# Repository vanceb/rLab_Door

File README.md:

# rLab_Door
A microcontroller project to allow members access to rLab

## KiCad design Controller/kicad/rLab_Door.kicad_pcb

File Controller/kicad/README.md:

# Production

## Kikit

Instructions for [kikit JLCPCB](https://github.com/yaqwsx/KiKit/blob/master/doc/fabrication/jlcpcb.md)

~~~sh
kikit fab jlcpcb --assembly --schematic rLab_Door.kicad_sch rLab_Door.kicad_pcb kikit_fab
~~~

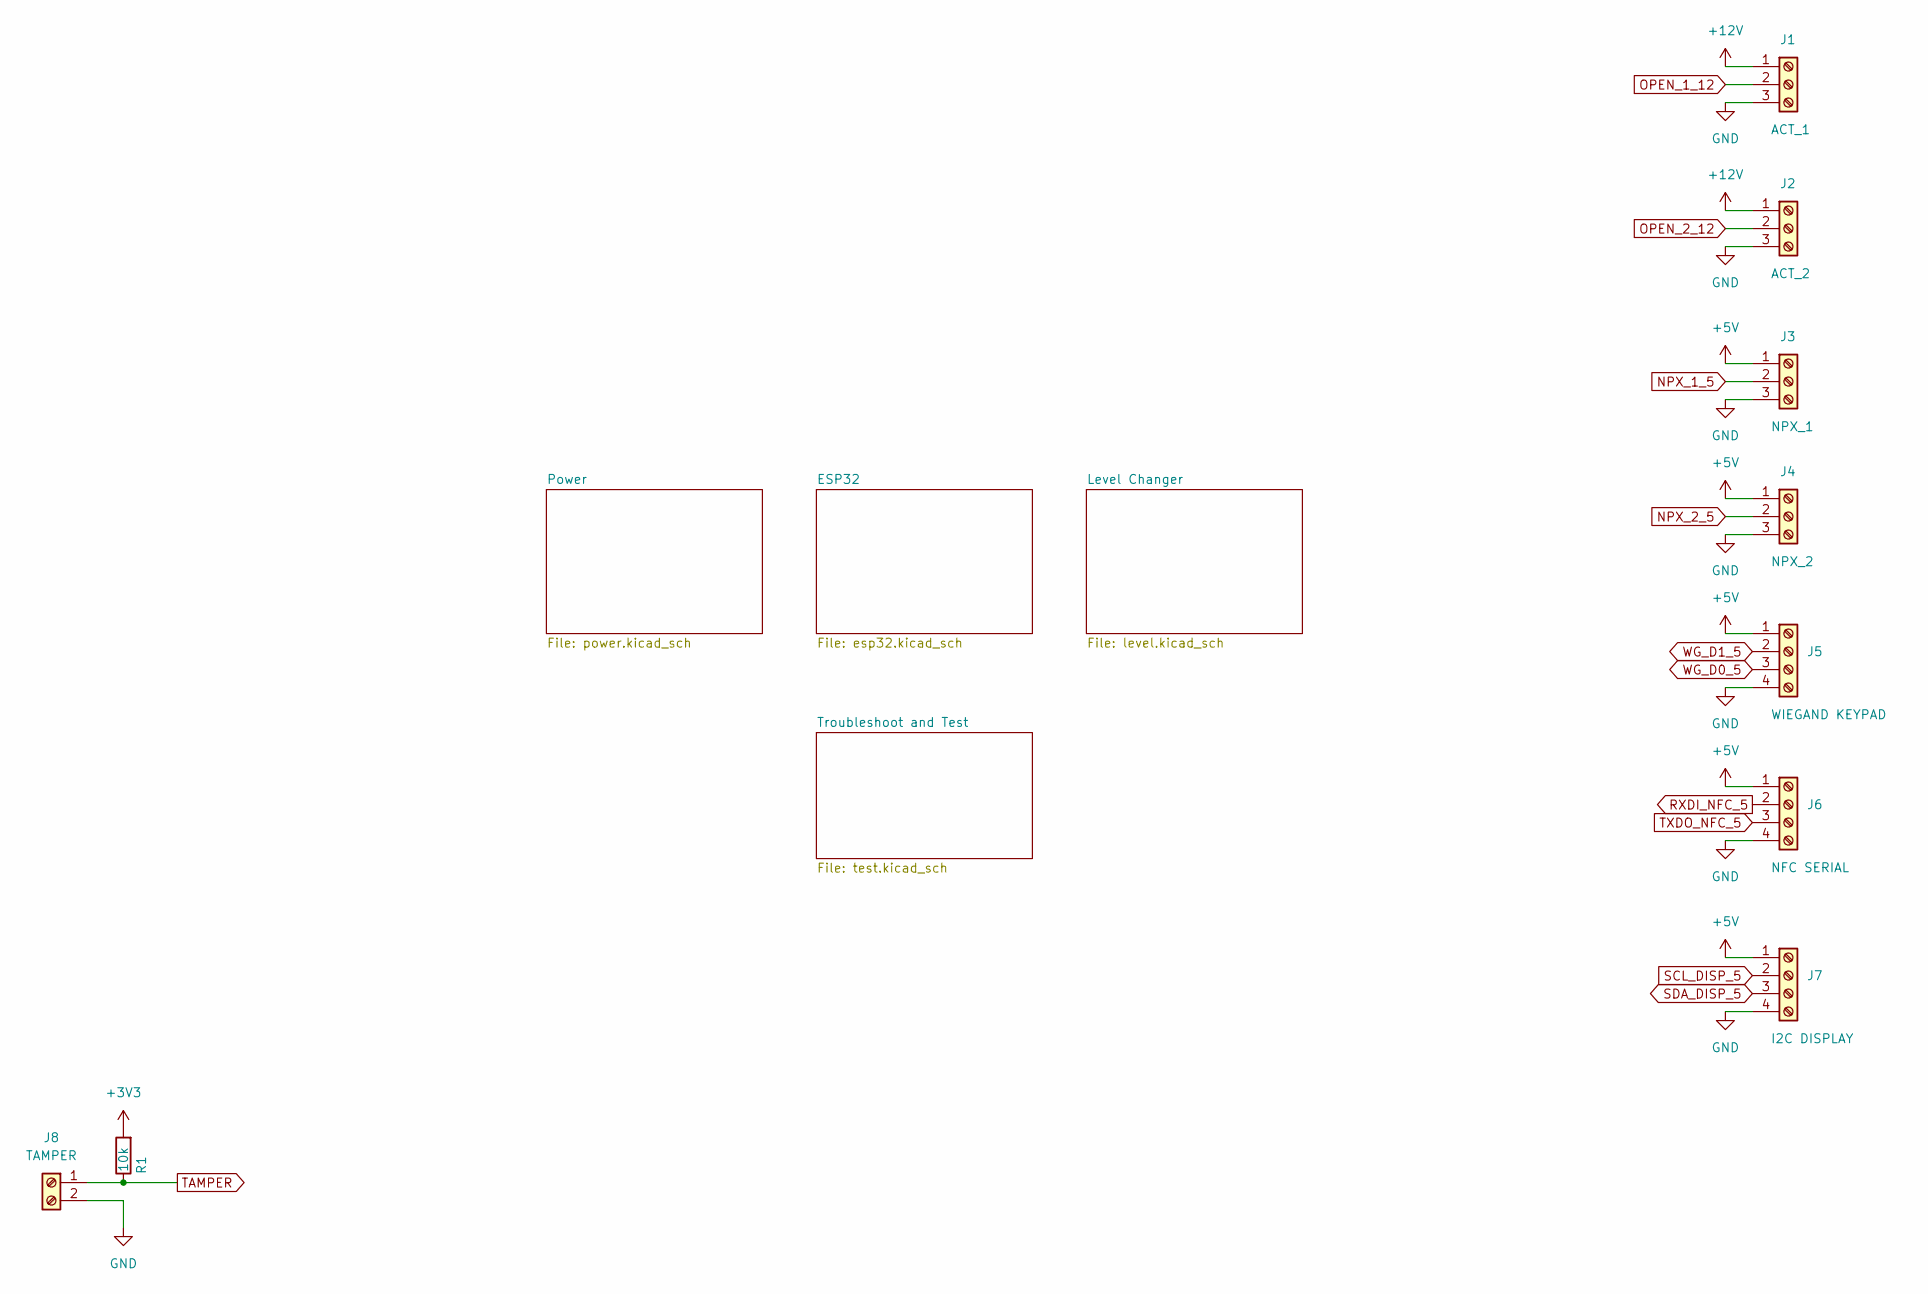
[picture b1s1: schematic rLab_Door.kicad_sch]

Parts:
J1: ACT_1; PinHeader_1x03_P2.54mm_Horizontal
J2: ACT_2; PinHeader_1x03_P2.54mm_Horizontal
J3: NPX_1; PinHeader_1x03_P2.54mm_Horizontal
J4: NPX_2; PinHeader_1x03_P2.54mm_Horizontal
J5: WIEGAND KEYPAD; PinHeader_1x04_P2.54mm_Horizontal
J6: NFC SERIAL; PinHeader_1x04_P2.54mm_Horizontal
J7: I2C DISPLAY; PinHeader_1x04_P2.54mm_Horizontal
J8: TAMPER; PinHeader_1x02_P2.54mm_Horizontal
R1: 10k; R_0603_1608Metric; LCSC C25804

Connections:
+3V3: R1.2; also elsewhere on the board
+5V: J3.1, J4.1, J5.1, J6.1, J7.1; also elsewhere on the board
+12V: J1.1, J2.1; also elsewhere on the board
GND: J1.3, J2.3, J3.3, J4.3, J5.4, J6.4, J7.4, J8.2; also elsewhere on the board
NPX_1_5: J3.2; also elsewhere on the board
NPX_2_5: J4.2; also elsewhere on the board
OPEN_1_12: J1.2; also elsewhere on the board
OPEN_2_12: J2.2; also elsewhere on the board
RXDI_NFC_5: J6.2; also elsewhere on the board
SCL_DISP_5: J7.2; also elsewhere on the board
SDA_DISP_5: J7.3; also elsewhere on the board
TAMPER: J8.1, R1.1; also elsewhere on the board
TXDO_NFC_5: J6.3; also elsewhere on the board
WG_D0_5: J5.3; also elsewhere on the board
WG_D1_5: J5.2; also elsewhere on the board

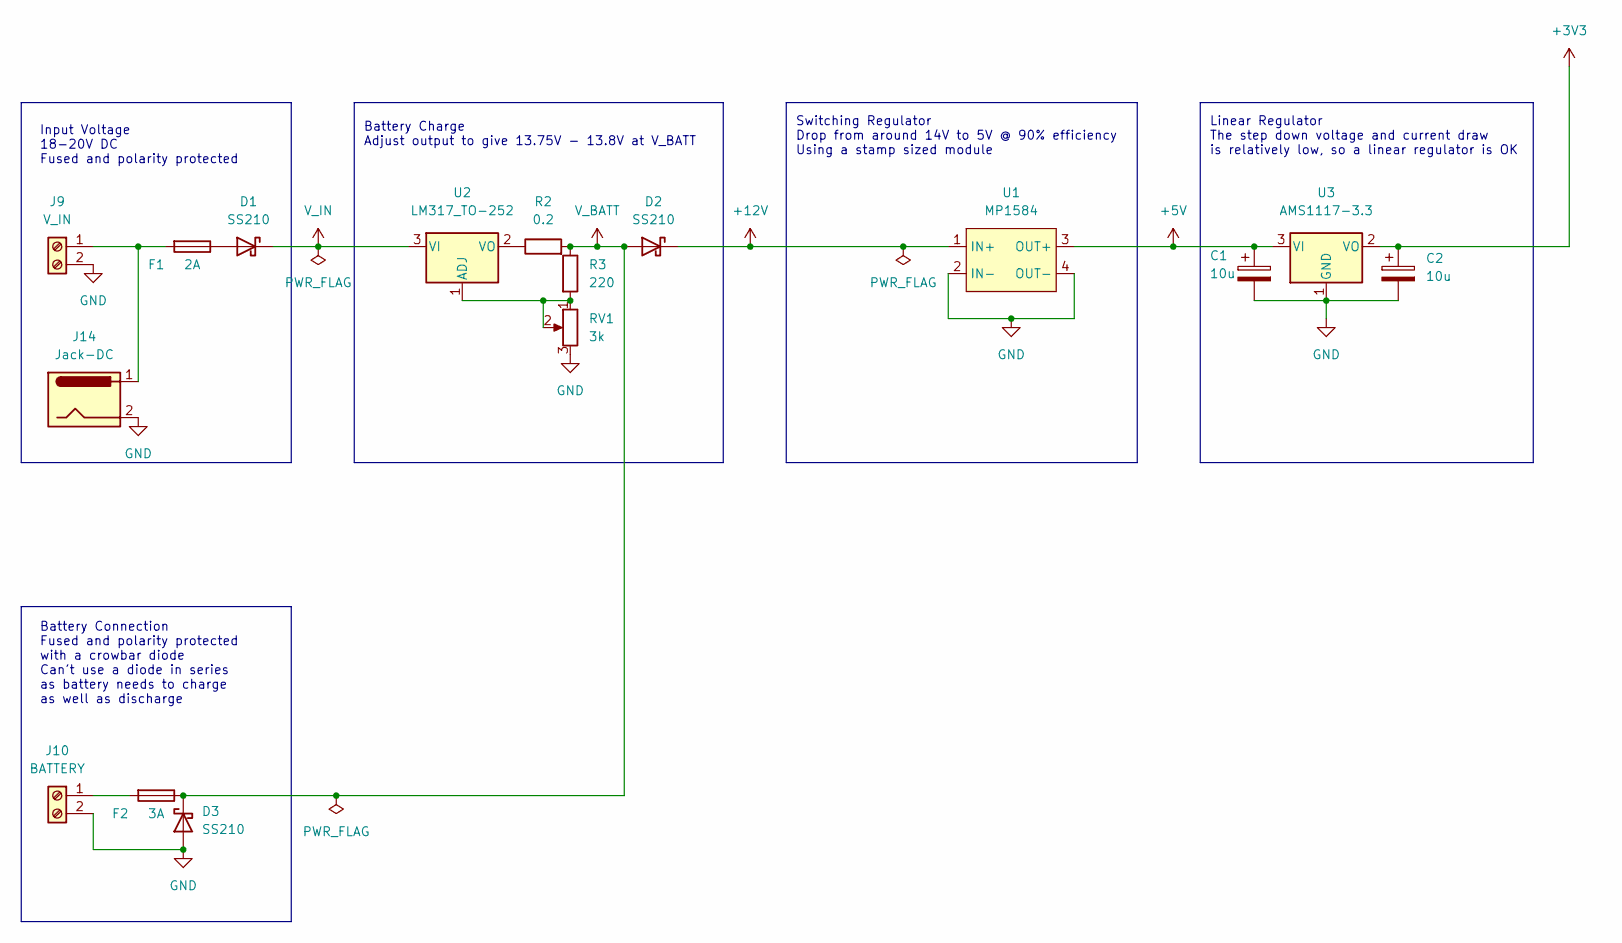
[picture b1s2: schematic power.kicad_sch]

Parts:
C1, C2: 10u; CP_EIA-3216-18_Kemet-A; LCSC C7171
D1, D2, D3: SS210; D_SMA; LCSC C14996
F1: 2A; Fuseholder_Cylinder-5x20mm_Schurter_0031_8201_Horizontal_Op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
F2: 3A; Fuseholder_Cylinder-5x20mm_Schurter_0031_8201_Horizontal_Op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
J9: V_IN; PinHeader_1x02_P2.54mm_Horizontal
J10: BATTERY; PinHeader_1x02_P2.54mm_Horizontal
J14: Jack-DC; BarrelJack_Horizontal
R2: 0.2; R_2512_6332Metric_Pad1.40x3.35mm_HandSolder; LCSC C841782
R3: 220; R_0603_1608Metric; LCSC C22962
RV1: 3k; Potentiometer_Bourns_3296W_Vertical
U1: MP1584
U2: LM317_TO-252; TO-252-2; LCSC C75510
U3: AMS1117-3.3; SOT-223-3_TabPin2; LCSC C6186

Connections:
+3V3: C2.1, U3.2 (VO); also elsewhere on the board
+5V: C1.1, U1.3 (OUT+), U3.3 (VI); also elsewhere on the board
+12V: D2.1 (K), U1.1 (IN+); also elsewhere on the board
GND: C1.2, C2.2, D3.2 (A), J9.2, J10.2, J14.2, RV1.3, U1.2 (IN-), U1.4 (OUT-), U3.1 (GND); also elsewhere on the board
unnamed: D1.2 (A), F1.1
unnamed: F1.2, J9.1, J14.1
unnamed: F2.2, J10.1
unnamed: R2.1, U2.2 (VO)
unnamed: R3.2, RV1.1, RV1.2, U2.1 (ADJ)
V_BATT: D2.2 (A), D3.1 (K), F2.1, R2.2, R3.1; also elsewhere on the board
V_IN: D1.1 (K), U2.3 (VI); also elsewhere on the board

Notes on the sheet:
Battery Charge Adjust output to give 13.75V - 13.8V at V_BATT
Linear Regulator The step down voltage and current draw is relatively low, so a linear regulator is OK
Battery Connection Fused and polarity protected with a crowbar diode Can't use a diode in series as battery needs to charge as well as discharge
Switching Regulator Drop from around 14V to 5V @ 90% efficiency Using a stamp sized module
Input Voltage 18-20V DC Fused and polarity protected

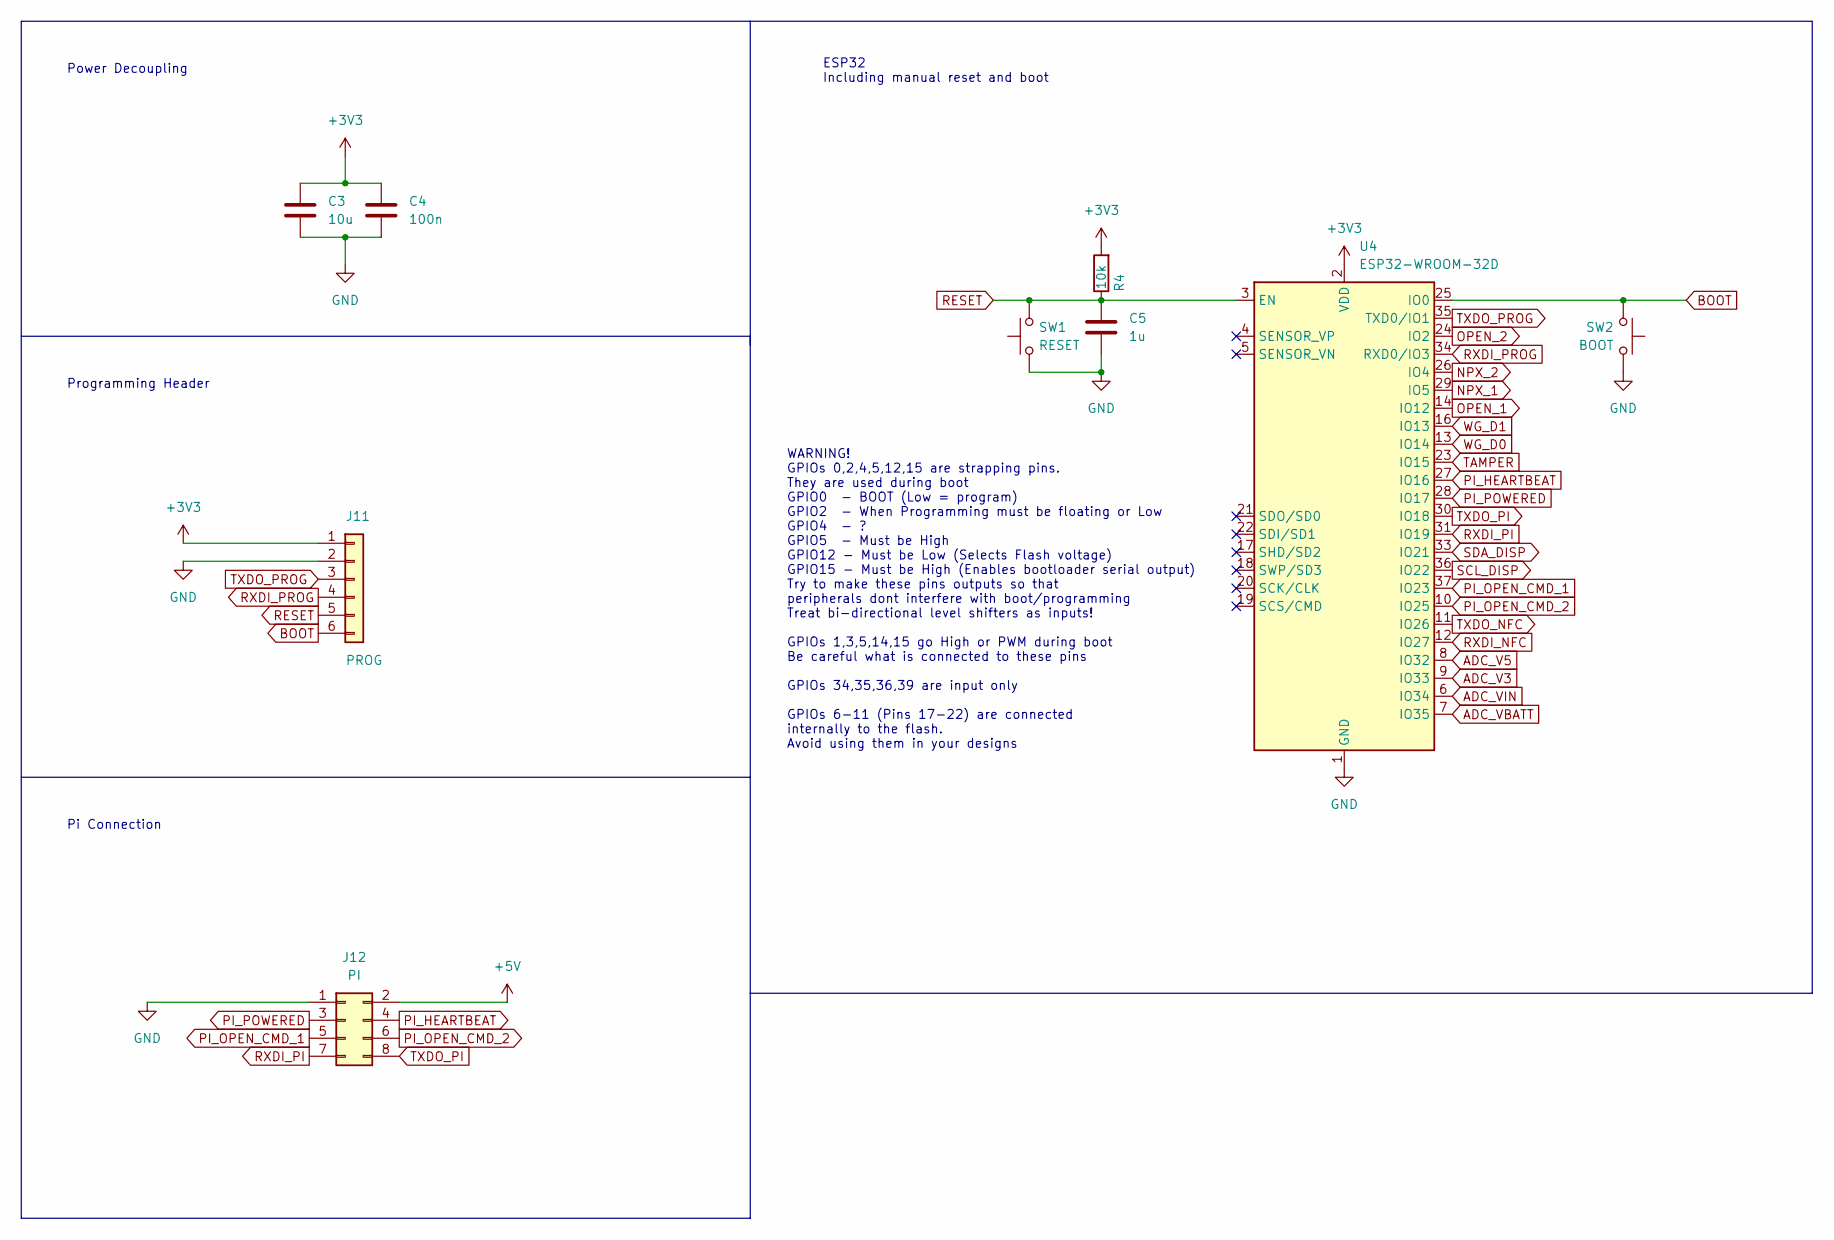
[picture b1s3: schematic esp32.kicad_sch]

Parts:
C3: 10u; C_1206_3216Metric; LCSC C13585
C4: 100n; C_0603_1608Metric; LCSC C14663
C5: 1u; C_0603_1608Metric; LCSC C15849
J11: PROG; PinHeader_1x06_P2.54mm_Vertical
J12: PI; IDC-Header_2x04_P2.54mm_Vertical
R4: 10k; R_0603_1608Metric; LCSC C25804
SW1: RESET; SW_Push_1P1T_NO_CK_KSC7xxJ; LCSC C318884
SW2: BOOT; SW_Push_1P1T_NO_CK_KSC7xxJ; LCSC C318884
U4: ESP32-WROOM-32D; ESP32-WROOM-32; LCSC C473012

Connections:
+3V3: C3.1, C4.1, J11.1, R4.2, U4.2 (VDD); also elsewhere on the board
+5V: J12.2; also elsewhere on the board
ADC_V3: U4.9 (IO33); also elsewhere on the board
ADC_V5: U4.8 (IO32); also elsewhere on the board
ADC_VBATT: U4.7 (IO35); also elsewhere on the board
ADC_VIN: U4.6 (IO34); also elsewhere on the board
BOOT: J11.6, SW2.2, U4.25 (IO0)
GND: C3.2, C4.2, C5.2, J11.2, J12.1, SW1.1, SW2.1, U4.1 (GND), U4.15 (GND), U4.38 (GND), U4.39 (GND); also elsewhere on the board
NPX_1: U4.29 (IO5); also elsewhere on the board
NPX_2: U4.26 (IO4); also elsewhere on the board
OPEN_1: U4.14 (IO12); also elsewhere on the board
OPEN_2: U4.24 (IO2); also elsewhere on the board
PI_HEARTBEAT: J12.4, U4.27 (IO16)
PI_OPEN_CMD_1: J12.5, U4.37 (IO23)
PI_OPEN_CMD_2: J12.6, U4.10 (IO25)
PI_POWERED: J12.3, U4.28 (IO17)
RESET: C5.1, J11.5, R4.1, SW1.2, U4.3 (EN)
RXDI_NFC: U4.12 (IO27); also elsewhere on the board
RXDI_PI: J12.7, U4.31 (IO19)
RXDI_PROG: J11.4, U4.34 (RXD0/IO3)
SCL_DISP: U4.36 (IO22); also elsewhere on the board
SDA_DISP: U4.33 (IO21); also elsewhere on the board
TAMPER: U4.23 (IO15); also elsewhere on the board
TXDO_NFC: U4.11 (IO26); also elsewhere on the board
TXDO_PI: J12.8, U4.30 (IO18)
TXDO_PROG: J11.3, U4.35 (TXD0/IO1)
WG_D0: U4.13 (IO14); also elsewhere on the board
WG_D1: U4.16 (IO13); also elsewhere on the board

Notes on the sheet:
Pi Connection
ESP32 Including manual reset and boot
Programming Header
WARNING! GPIOs 0,2,4,5,12,15 are strapping pins. They are used during boot GPIO0 - BOOT (Low = program) GPIO2 - When Programming must be floating or Low GPIO4 - ? GPIO5 - Must be High GPIO12 - Must be Low (Selects Flash voltage) GPIO15 - Must be High (Enables bootloader serial output) Try to make t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
Power Decoupling

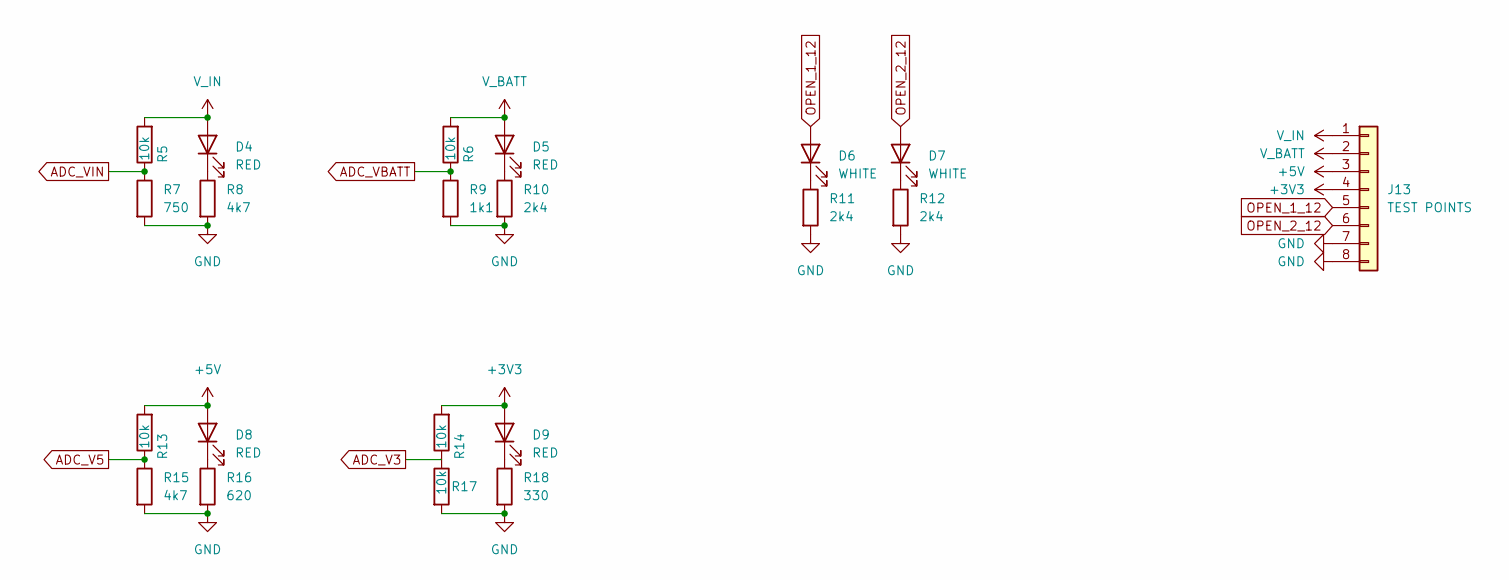
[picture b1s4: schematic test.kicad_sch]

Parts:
D4, D5, D8, D9: RED; LED_0603_1608Metric; LCSC C2286
D6, D7: WHITE; LED_0603_1608Metric; LCSC C2290
J13: TEST POINTS; PinHeader_1x08_P2.54mm_Vertical
R5, R6, R13, R14, R17: 10k; R_0603_1608Metric; LCSC C25804
R7: 750; R_0603_1608Metric; LCSC C23241
R8, R15: 4k7; R_0603_1608Metric; LCSC C23162
R9: 1k1; R_0603_1608Metric; LCSC C22764
R10, R11, R12: 2k4; R_0603_1608Metric; LCSC C22940
R16: 620; R_0603_1608Metric; LCSC C23220
R18: 330; R_0603_1608Metric; LCSC C23138

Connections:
+3V3: D9.2 (A), J13.4, R14.2; also elsewhere on the board
+5V: D8.2 (A), J13.3, R13.2; also elsewhere on the board
ADC_V3: R14.1, R17.1; also elsewhere on the board
ADC_V5: R13.1, R15.1; also elsewhere on the board
ADC_VBATT: R6.1, R9.1; also elsewhere on the board
ADC_VIN: R5.1, R7.1; also elsewhere on the board
GND: J13.7, J13.8, R7.2, R8.2, R9.2, R10.2, R11.2, R12.2, R15.2, R16.2, R17.2, R18.2; also elsewhere on the board
unnamed: D4.1 (K), R8.1
unnamed: D5.1 (K), R10.1
unnamed: D6.1 (K), R11.1
unnamed: D7.1 (K), R12.1
unnamed: D8.1 (K), R16.1
unnamed: D9.1 (K), R18.1
OPEN_1_12: D6.2 (A), J13.5; also elsewhere on the board
OPEN_2_12: D7.2 (A), J13.6; also elsewhere on the board
V_BATT: D5.2 (A), J13.2, R6.2; also elsewhere on the board
V_IN: D4.2 (A), J13.1, R5.2; also elsewhere on the board

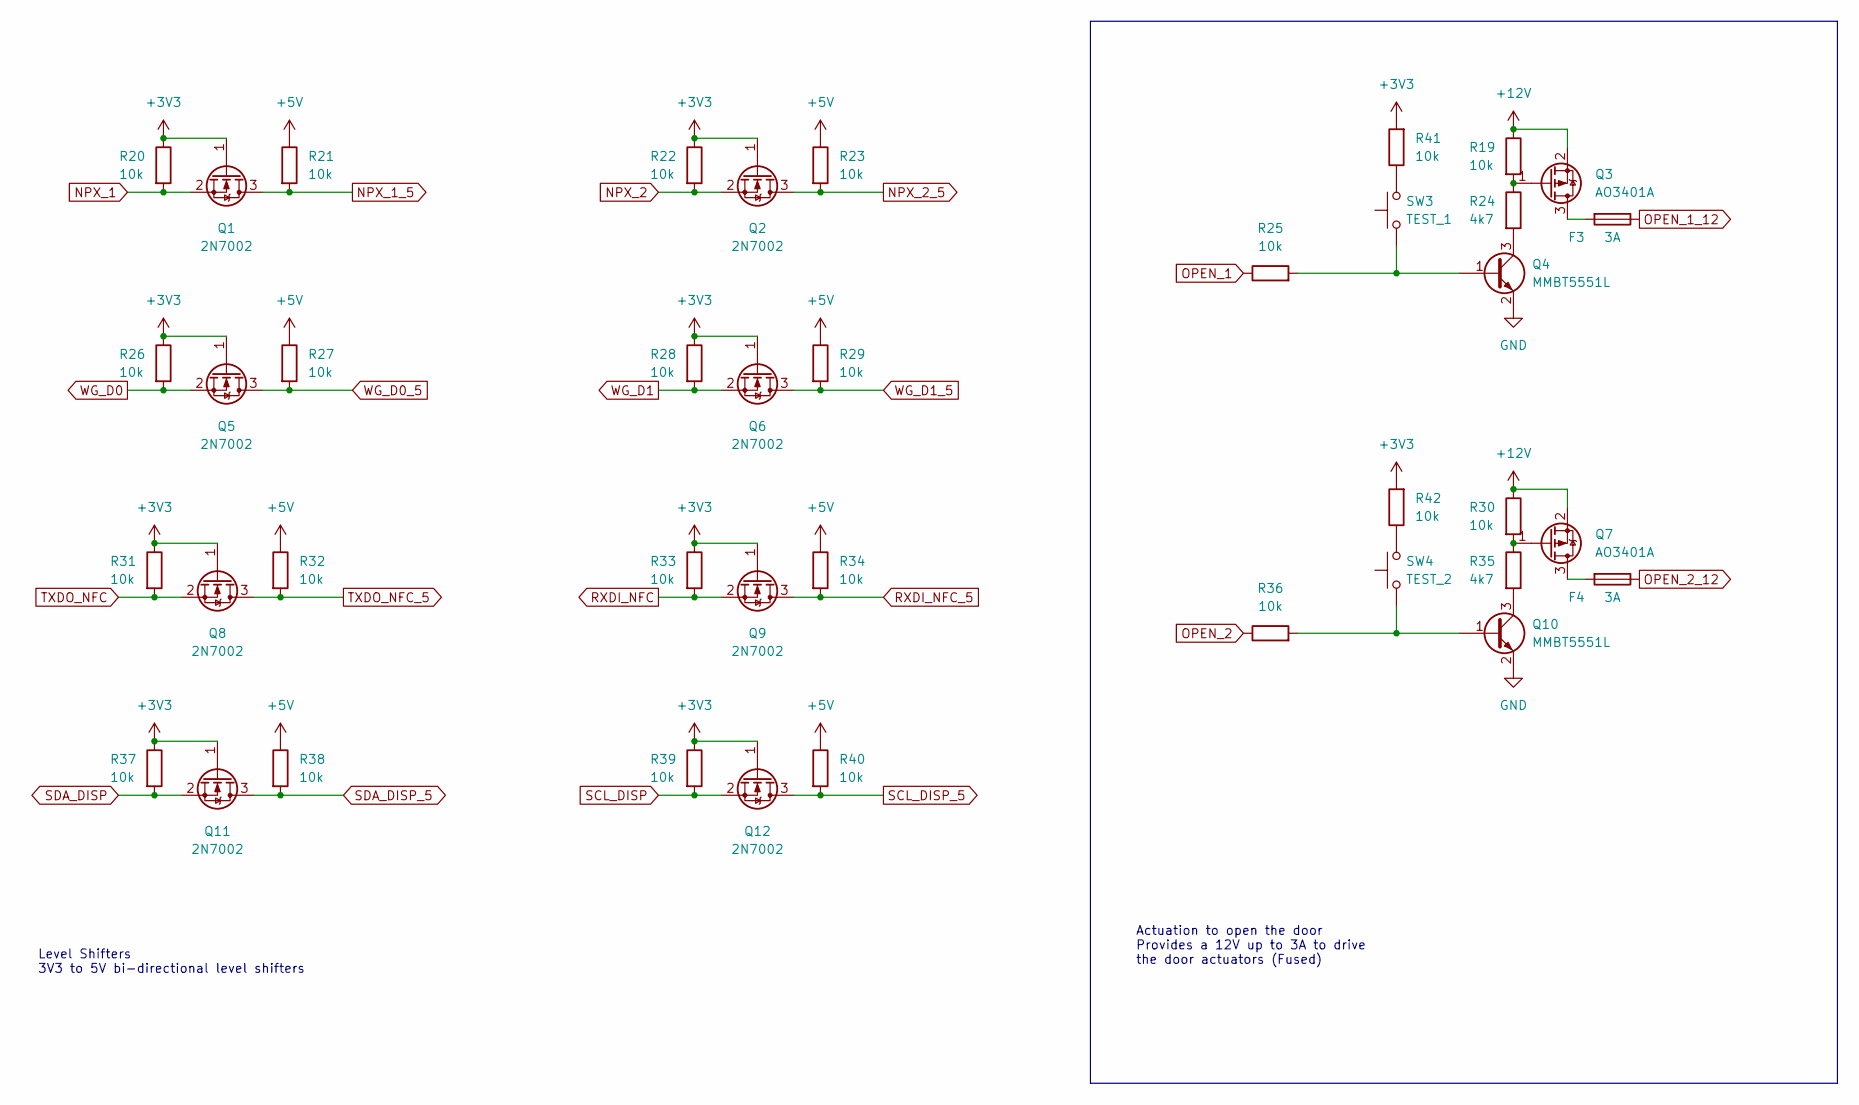
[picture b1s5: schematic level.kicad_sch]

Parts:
F3, F4: 3A; Fuseholder_Cylinder-5x20mm_Schurter_0031_8201_Horizontal_Op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
Q1, Q2, Q5, Q6, Q8, Q9, Q11, Q12: 2N7002; SOT-23; LCSC C8545
Q3, Q7: AO3401A; SOT-23; LCSC C15127
Q4, Q10: MMBT5551L; SOT-23; LCSC C2145
R19, R20, R21, R22, R23, R25, R26, R27, R28, R29, R30, R31, R32, R33, R34, R36, R37, R38, R39, R40, R41, R42: 10k; R_0603_1608Metric; LCSC C25804
R24, R35: 4k7; R_0603_1608Metric; LCSC C23162
SW3: TEST_1; SW_Push_1P1T_NO_CK_KSC7xxJ; LCSC C318884
SW4: TEST_2; SW_Push_1P1T_NO_CK_KSC7xxJ; LCSC C318884

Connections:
+3V3: Q1.1 (G), Q2.1 (G), Q5.1 (G), Q6.1 (G), Q8.1 (G), Q9.1 (G), Q11.1 (G), Q12.1 (G), R20.1, R22.1, R26.1, R28.1, R31.1, R33.1, R37.1, R39.1, R41.2, R42.2; also elsewhere on the board
+5V: R21.1, R23.1, R27.1, R29.1, R32.1, R34.1, R38.1, R40.1; also elsewhere on the board
+12V: Q3.2 (S), Q7.2 (S), R19.1, R30.1; also elsewhere on the board
GND: Q4.2 (E), Q10.2 (E); also elsewhere on the board
NPX_1: Q1.2 (S), R20.2; also elsewhere on the board
NPX_1_5: Q1.3 (D), R21.2; also elsewhere on the board
NPX_2: Q2.2 (S), R22.2; also elsewhere on the board
NPX_2_5: Q2.3 (D), R23.2; also elsewhere on the board
unnamed: F3.2, Q3.3 (D)
unnamed: F4.2, Q7.3 (D)
unnamed: Q3.1 (G), R19.2, R24.1
unnamed: Q4.1 (B), R25.2, SW3.1
unnamed: Q4.3 (C), R24.2
unnamed: Q7.1 (G), R30.2, R35.1
unnamed: Q10.1 (B), R36.2, SW4.1
unnamed: Q10.3 (C), R35.2
unnamed: R41.1, SW3.2
unnamed: R42.1, SW4.2
OPEN_1: R25.1; also elsewhere on the board
OPEN_1_12: F3.1; also elsewhere on the board
OPEN_2: R36.1; also elsewhere on the board
OPEN_2_12: F4.1; also elsewhere on the board
RXDI_NFC: Q9.2 (S), R33.2; also elsewhere on the board
RXDI_NFC_5: Q9.3 (D), R34.2; also elsewhere on the board
SCL_DISP: Q12.2 (S), R39.2; also elsewhere on the board
SCL_DISP_5: Q12.3 (D), R40.2; also elsewhere on the board
SDA_DISP: Q11.2 (S), R37.2; also elsewhere on the board
SDA_DISP_5: Q11.3 (D), R38.2; also elsewhere on the board
TXDO_NFC: Q8.2 (S), R31.2; also elsewhere on the board
TXDO_NFC_5: Q8.3 (D), R32.2; also elsewhere on the board
WG_D0: Q5.2 (S), R26.2; also elsewhere on the board
WG_D0_5: Q5.3 (D), R27.2; also elsewhere on the board
WG_D1: Q6.2 (S), R28.2; also elsewhere on the board
WG_D1_5: Q6.3 (D), R29.2; also elsewhere on the board

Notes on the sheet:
Level Shifters 3V3 to 5V bi-directional level shifters
Actuation to open the door Provides a 12V up to 3A to drive the door actuators (Fused)

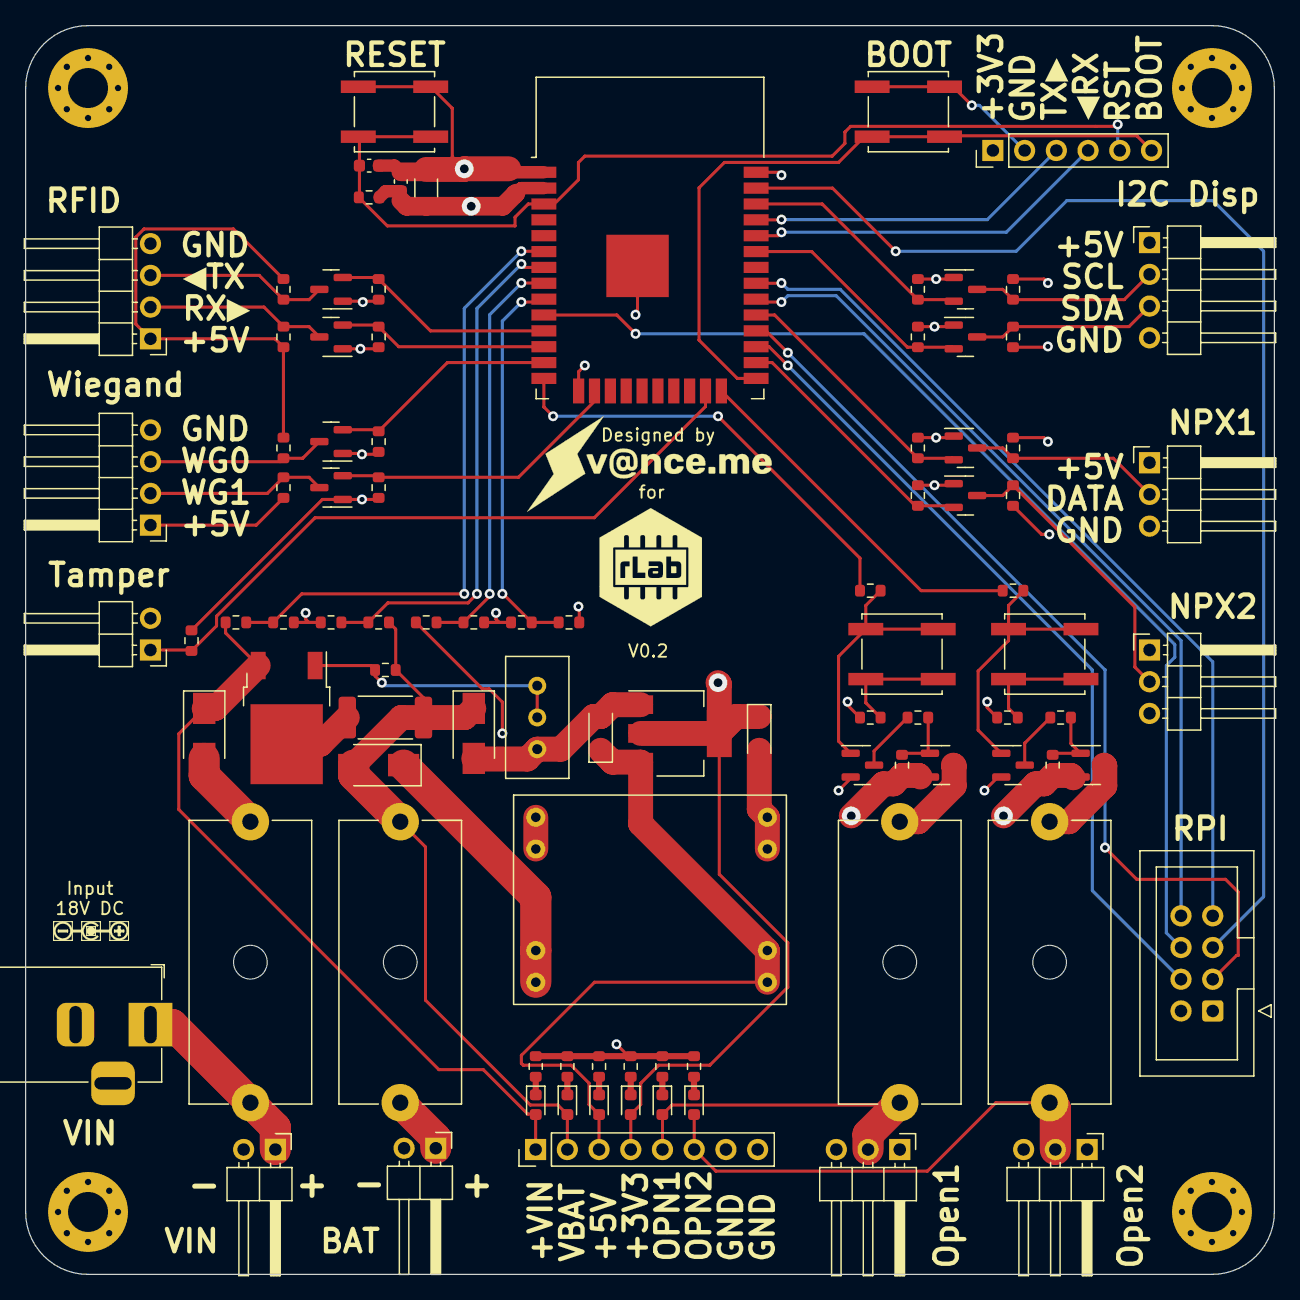
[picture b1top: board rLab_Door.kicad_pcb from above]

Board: 4 copper layers, 100.0 x 100.0 mm, 95 parts (0 on the bottom side), 62 nets.

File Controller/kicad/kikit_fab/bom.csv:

Comment,Designator,Footprint,LCSC
10u,"C1,C2",Capacitor_Tantalum_SMD:CP_EIA-3216-18_Kemet-A,C7171
10u,C3,Capacitor_SMD:C_1206_3216Metric,C13585
100n,C4,Capacitor_SMD:C_0603_1608Metric,C14663
1u,C5,Capacitor_SMD:C_0603_1608Metric,C15849
SS210,"D1,D2,D3",Diode_SMD:D_SMA,C14996
RED,"D4,D5,D8,D9",LED_SMD:LED_0603_1608Metric,C2286
WHITE,"D6,D7",LED_SMD:LED_0603_1608Metric,C2290
2A,F1,Fuse:Fuseholder_Cylinder-5x20mm_Schurter_0031_8201_Horizontal_Open,
3A,"F2,F3,F4",Fuse:Fuseholder_Cylinder-5x20mm_Schurter_0031_8201_Horizontal_Open,
ACT_1,J1,Connector_PinHeader_2.54mm:PinHeader_1x03_P2.54mm_Horizontal,
ACT_2,J2,Connector_PinHeader_2.54mm:PinHeader_1x03_P2.54mm_Horizontal,
NPX_1,J3,Connector_PinHeader_2.54mm:PinHeader_1x03_P2.54mm_Horizontal,
NPX_2,J4,Connector_PinHeader_2.54mm:PinHeader_1x03_P2.54mm_Horizontal,
WIEGAND KEYPAD,J5,Connector_PinHeader_2.54mm:PinHeader_1x04_P2.54mm_Horizontal,
NFC SERIAL,J6,Connector_PinHeader_2.54mm:PinHeader_1x04_P2.54mm_Horizontal,
I2C DISPLAY,J7,Connector_PinHeader_2.54mm:PinHeader_1x04_P2.54mm_Horizontal,
TAMPER,J8,Connector_PinHeader_2.54mm:PinHeader_1x02_P2.54mm_Horizontal,
V_IN,J9,Connector_PinHeader_2.54mm:PinHeader_1x02_P2.54mm_Horizontal,
BATTERY,J10,Connector_PinHeader_2.54mm:PinHeader_1x02_P2.54mm_Horizontal,
PROG,J11,Connector_PinHeader_2.54mm:PinHeader_1x06_P2.54mm_Vertical,
PI,J12,Connector_IDC:IDC-Header_2x04_P2.54mm_Vertical,
TEST POINTS,J13,Connector_PinHeader_2.54mm:PinHeader_1x08_P2.54mm_Vertical,
Jack-DC,J14,Connector_BarrelJack:BarrelJack_Horizontal,
2N7002,"Q1,Q2,Q5,Q6,Q8,Q9,Q11,Q12",Package_TO_SOT_SMD:SOT-23,C8545
AO3401A,"Q3,Q7",Package_TO_SOT_SMD:SOT-23,C15127
MMBT5551L,"Q4,Q10",Package_TO_SOT_SMD:SOT-23,C2145
10k,"R1,R4,R5,R6,R13,R14,R17,R19,R20,R21,R22,R23,R25,R26,R27,R28,R29,R30,R31,R32,R33,R34,R36,R37,R38,R39,R40,R41,R42",Resistor_SMD:R_0603_1608Metric,C25804
0.2,R2,Resistor_SMD:R_2512_6332Metric_Pad1.40x3.35mm_HandSolder,C841782
220,R3,Resistor_SMD:R_0603_1608Metric,C22962
750,R7,Resistor_SMD:R_0603_1608Metric,C23241
4k7,"R8,R15,R24,R35",Resistor_SMD:R_0603_1608Metric,C23162
1k1,R9,Resistor_SMD:R_0603_1608Metric,C22764
2k4,"R10,R11,R12",Resistor_SMD:R_0603_1608Metric,C22940
620,R16,Resistor_SMD:R_0603_1608Metric,C23220
330,R18,Resistor_SMD:R_0603_1608Metric,C23138
3k,RV1,Potentiometer_THT:Potentiometer_Bourns_3296W_Vertical,
RESET,SW1,Button_Switch_SMD:SW_Push_1P1T_NO_CK_KSC7xxJ,C318884
BOOT,SW2,Button_Switch_SMD:SW_Push_1P1T_NO_CK_KSC7xxJ,C318884
TEST_1,SW3,Button_Switch_SMD:SW_Push_1P1T_NO_CK_KSC7xxJ,C318884
TEST_2,SW4,Button_Switch_SMD:SW_Push_1P1T_NO_CK_KSC7xxJ,C318884
MP1584,U1,MP1584:MP1584,
LM317_TO-252,U2,Package_TO_SOT_SMD:TO-252-2,C75510
AMS1117-3.3,U3,Package_TO_SOT_SMD:SOT-223-3_TabPin2,C6186
ESP32-WROOM-32D,U4,RF_Module:ESP32-WROOM-32,C473012

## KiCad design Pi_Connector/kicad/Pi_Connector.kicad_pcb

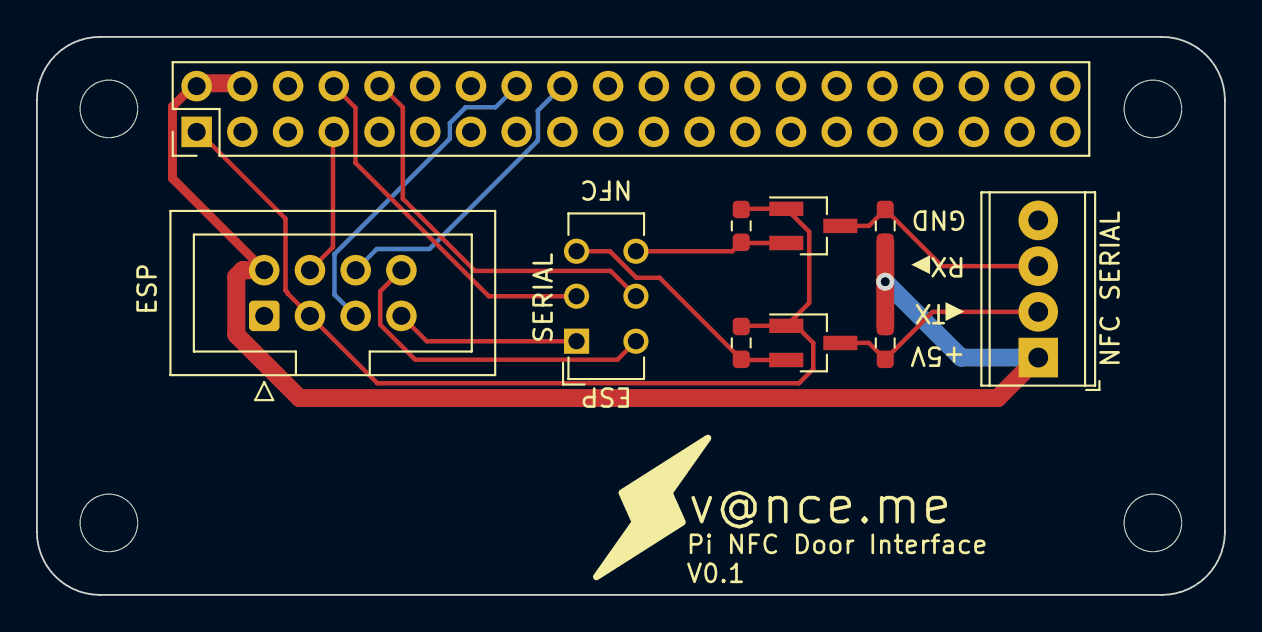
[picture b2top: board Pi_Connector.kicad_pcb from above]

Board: 2 copper layers, 66.0 x 31.0 mm, 10 parts (0 on the bottom side), 14 nets.

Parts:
J1: PI; IDC-Header_2x04_P2.54mm_Vertical
J2: Conn_02x20_Odd_Even; PinHeader_2x20_P2.54mm_Vertical
J3: NFC SERIAL; TerminalBlock_Phoenix_MPT-0,5-4-2.54_1x04_P2.54mm_Horizontal
Q1, Q2: 2N7002; SOT-23_Handsoldering
R1, R2, R3, R4: 10k; R_0603_1608Metric_Pad0.98x0.95mm_HandSolder
SW1: SW_DPDT_x2; SW_CuK_JS202011CQN_DPDT_Straight

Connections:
+5V: J1.2, J2.2, J2.4, J3.1, R2.1, R4.1
GND: J1.1, J2.6, J2.9, J2.14, J2.20, J2.25, J2.30, J2.34, J2.39, J3.4
PI_HEARTBEAT: J1.4, J2.7
PI_OPEN_CMD_1: J1.5, J2.16
PI_OPEN_CMD_2: J1.6, J2.18
PI_POWERED: J1.3, J2.1, Q1.1 (G), Q2.1 (G), R1.1, R3.1
RXDI: J2.10, SW1.5 (B)
RXDI_ESP: J1.8, SW1.4 (A)
RXDI_NFC: Q2.2 (S), R3.2, SW1.6 (C)
RXDI_NFC_5: J3.3, Q2.3 (D), R4.2
TXDO: J2.8, SW1.2 (B)
TXDO_ESP: J1.7, SW1.1 (A)
TXDO_NFC: Q1.2 (S), R1.2, SW1.3 (C)
TXDO_NFC_5: J3.2, Q1.3 (D), R2.2

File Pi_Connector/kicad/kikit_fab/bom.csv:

Comment,Designator,Footprint,LCSC
PI,J1,Connector_IDC:IDC-Header_2x04_P2.54mm_Vertical,
Conn_02x20_Odd_Even,J2,Connector_PinHeader_2.54mm:PinHeader_2x20_P2.54mm_Vertical,
NFC SERIAL,J3,"TerminalBlock_Phoenix:TerminalBlock_Phoenix_MPT-0,5-4-2.54_1x04_P2.54mm_Horizontal",
2N7002,"Q1,Q2",Package_TO_SOT_SMD:SOT-23_Handsoldering,C8545
10k,"R1,R2,R3,R4",Resistor_SMD:R_0603_1608Metric_Pad0.98x0.95mm_HandSolder,C25804
SW_DPDT_x2,SW1,Button_Switch_THT:SW_CuK_JS202011CQN_DPDT_Straight,

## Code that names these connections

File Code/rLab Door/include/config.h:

#ifndef CONFIG_H
#define CONFIG_H

/* GPIO config */

/* UARTs */
/* Serial - Standard pinouts for programming/logging */
#define GPIO_TXDO_PROG       1
#define GPIO_RXDI_PROG       3
/* Serial2 - Raspberry Pi Serial Interface */
#define GPIO_TXDO_PI         18
#define GPIO_RXDI_PI         19
/* Serial3 - NFC Serial Interface */
#define GPIO_TXDO_NFC        26
#define GPIO_RXDI_NFC        27

/* Raspberry Pi */
#define GPIO_PI_HEARTBEAT    16
#define GPIO_PI_POWERED      17
#define GPIO_PI_OPEN_CMD_1   23
#define GPIO_PI_OPEN_CMD_2   25

/* Monitoring */
#define GPIO_TAMPER          15
#define GPIO_ADC_VIN         35
#define GPIO_ADC_VBATT       34
#define GPIO_ADC_V5          32
#define GPIO_ADC_V3          33

/* Display */
#define GPIO_NPX_1           5
#define GPIO_NPX_2           4
#define GPIO_SDA_DISP        21
#define GPIO_SCL_DISP        22

/* Control */
#define GPIO_OPEN_1          13
#define GPIO_OPEN_2          2

/* Keypad */
#define GPIO_WGD0            14
#define GPIO_WGD1            12


/* I2C Character Display */
#define DISP_ADDR           0x27
#define DISP_ROWS           4
#define DISP_COLS           20

/* Max variable string lengths */
/* Wifi */
#define WIFI_SSID_MAX_LEN   16
#define WIFI_PASSWD_MAX_LEN 32
/* Pushover (https://pushover.net) */
#define PO_USER_KEY_MAX_LEN 32
#define PO_API_KEY_MAX_LEN  32

/* Preferences stored (Flash) */
#define PREFS_NS            "rlabDoor"

#define PREFS_WIFI_SSID_KEY "wifi_ssid"
#define PREFS_WIFI_PWD_KEY  "wifi_passwd"
#define PREFS_HARDWARE_KEY  "hw_enabled"

/* Hardware Enabled Bits */
#define ENABLED_PI          0x01    // Monitor and accept commands from the Pi
#define ENABLED_DISP        0x02    // Send messages to character display
#define ENABLED_NPX_1       0x04    // Drive neopixel string 1
#define ENABLED_NPX_2       0x08    // Drive neopixel string 2
#define ENABLED_OPEN_2      0x10    // OPEN_1 always enabled
#define ENABLED_KEYPAD      0x20    // Accept input from the keypad
#define ENABLED_NFC         0x40    // Accept input from the NFC reader
#define ENABLED_WIFI        0x80    // Allow WiFi connectivity


#endif

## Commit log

2022-06-27 Updated docs
2022-06-27 Added .gitignore for kicad from github
2022-06-27 Board files ready for the generation of fabrication outputs
2022-06-27 V0.1 fabrication files
2022-06-30 Rework of power circuits to improve protection
2022-06-30 Final check of ERC and DRC before fabrication outputs
2022-06-30 Improved V_IN and BATTERY traces to handle up to 4A current
2022-06-30 Generated gerbers for fabrication
2022-07-01 Initial design
2022-07-01 Created gerbers for fabrication
2022-07-01 Rounded corners of the board, added M3 mounting holes and recentered components
2022-07-01 Minor tweak to silkscreen abd generation of gerbers for fabrication
2022-07-01 Tweaked .gitignore to track bom.csv and pos.csv files needed for fabrication
2022-07-01 Updated .gitignore
2022-07-01 Added some vias to the high power connections to improve current capacity
2022-07-01 regenerated gerbers after changes to board
2022-07-01 Moved main board files into Controller/kicad
2022-07-02 Tweaked board to allow for JLCPCB standard assembly. Needed fiducials and 5mm rail clearance top and bottom. Also fixed silkscreen mistake
2022-07-03 Generated fabrication files
2022-07-03 A few more notes
2022-07-08 Initial code commit, simple notification working
2022-07-09 end of day check-in
2022-07-10 end of day
2022-07-14 End of day checkin - code compiles and works to a point
2022-07-14 Updated schematics based on issues and improvements from the prototype board
2022-07-18 Fault finding - this runs OK
2022-07-18 Still working
2022-07-19 Preferences storage broken
2022-07-20 Able to configure Pushover, but send 404s
2022-07-20 Sending Pushover messages successfully
2022-07-20 Tested pushover and improved help
2022-07-24 Added Pi control of the door
2022-07-25 Added system voltage monitoring
2022-07-25 Basic LCD Character display connected
2022-07-25 Battery charge tested, useful messages to character display. Disabled neopix and they seemed to hang the system
2022-07-26 Migrated pushover to use a queue
2022-07-26 Switched to Adafruit neopixel library
2022-07-26 Turned neopixels green if the door is opened
2022-07-29 Tidies u header files and dependencies
2022-07-29 Removed features package
2022-07-29 Attempted improvements to the display which was showing corruption
2022-07-29 Added log warnings into the voltage check code
2022-07-29 Updated display to include door status
2022-07-29 Tweaked display working from shut to lock
2022-08-16 RFID code added, but disabled (not working)
2022-08-16 Added comments to RFID issue, works without RFID
2022-08-25 Got basic working rfid PN532
2022-08-25 Updated schematic to fix issues with V1, including incorrect PCB layout for MP1584
2022-09-08 Pre-production check-in
2022-09-08 PCB save
2022-09-08 Production of V0.2
2022-09-25 First working version on V0.2 hardware
2022-11-02 Monor tweaks and the creation of STEP 3D Models for use in imechanical CAD
2022-11-02 Removing code to separate repository - rLab_Door_Code
